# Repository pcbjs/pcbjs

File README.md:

# pcbjs

PCB design as TypeScript and JSX. A board is a TSX module: nets and parts are values, JSX places them, and one compile routes what you leave to the autorouter, fills pours, runs DRC and ERC, and writes Gerbers, drills, a BOM and placement file, all zipped, plus a 2D, 3D and schematic viewer that links every item back to its code. This documentation targets pcbjs 0.1.0.

```sh
npm i -D @pcbjs/pcbjs    # Node 22.12 or newer
```

## Quick start

```sh
npx pcbjs create my-board && cd my-board && npm install
npx pcbjs check              # compile, route, DRC and ERC; one line per finding with the source line to change
npm run dev                  # live viewer on http://localhost:5173
npm run build                # fab set in .pcbjs/fab/my-board, site in .pcbjs/dist
```

`pcbjs create` writes this first board, `pcb.tsx`: a green LED and its resistor on a 20 x 15 mm two-layer board.

```tsx
// Hello: a green LED on a 20 x 15 mm two-layer board, powered from a two-pin header.
// Frame: millimetres, origin at the top-left corner of the outline, x right, y down.
import PCB from '@pcbjs/fab/JLCPCB/2-Layer' // the fab: stackup, rules and LCSC sourcing; swap for another preset such as @pcbjs/fab/OSHPark/2-Layer
import { nets, route } from '@pcbjs/core'
import { PinHeader, R0603, LED0603, roundedRect } from '@pcbjs/lib'

// Nets: one name per net.
const { GND, VCC, LED } = nets()

// Parts: the value, the part numbers, then the net of each pin by name. MPN is the catch-all, MPN:LCSC is what JLCPCB assembles.
const J1 = PinHeader(2)().source({ MPN: 'PEC02SAAN' }).connect({ 1: GND, 2: VCC })
const R1 = R0603('330').source({ MPN: 'RC0603FR-07330RL', 'MPN:LCSC': 'C23138' }).connect({ 1: VCC, 2: LED })
const D1 = LED0603('green').source({ MPN: 'LTST-C190GKT' }).connect({ A: LED, K: GND })

export default (
  <PCB name="Hello" rev="0.1.0">
    {/* outline: 20 x 15 mm with 1 mm corners */}
    <path layer="Edge.Cuts" d={roundedRect(20, 15, 1)} />

    {/* power in: pin 1 GND, pin 2 VCC */}
    <J1 at="3 4.96" />

    {/* the LED and its resistor, in line with J1 pin 2; D1 turned so its anode faces R1 */}
    <R1 at="9 7.5" />
    <D1 at="15 7.5 180deg" />

    {/* routes: .Z() draws a straight track by hand, a route with no chain is left to the autorouter */}
    {route(J1[2], R1[1]).width(0.3).Z()}
    {route(R1[2], D1.A).width(0.3).Z()}
    {route(D1.K, J1[1]).width(0.3)}

    {/* silk */}
    <text layer="F.SilkS" at="10 12" size={1}>
      Hello
    </text>
  </PCB>
)
```

More boards to start from: `npx pcbjs create --list-examples`, and `examples/demo` with Blinky, a board split into schematic, sourcing and layout files. From source, for contributors: clone https://github.com/pcbjs/pcbjs, run `npm install && npm run build`, and read docs/development.md.

## For agents

Read this section, then `pcbjs docs <topic>` for the one topic you need, which is `docs/<topic>.md` here and the same page under https://pcbjs.dev/docs/. Do not read the whole docs folder; `pcbjs docs --grep 'neck|escape'` prints every doc line that matches a word or a regex. `pcbjs skills install` adds the agent skills of `@pcbjs/skills` to the project and registers `pcbjs mcp`, whose tools a harness then prefers to the shell. `pcbjs docs check` reads the check output field by field; `pcbjs docs findings` lists every rule.

### Mental model

- Schematic: `nets()` gives `Net` values; a footprint factory with a value gives a `Part`; `.connect({ … })` binds pins to nets by name and throws at the call when a pin is wrong. Parts are values: make them in `.map` and plain functions, a loop part with `{ ref }`; the constant a part is bound to is its ref, `const R1 = …` is R1, and nothing is numbered.
- Layout: a part is placed as a JSX element, `<R1 at="9 7.5" />`, or `<Place part={LEDS[2]} at="…" />`; `<g name="P3">` makes `U8` also `P3/U8`.
- Routes: `route(a, b)` and a chain from `a`, `.H(x)`, `.via('B.Cu')`, finishing at `b` with `.Z()` for a straight track or, by default, an automatic leg the autorouter lays after everything else. More ends make a tree; `route('3 10').net(VCC).H(9)` is copper without pads.
- Build: one compile gives the board model, DRC, ERC, the fab set and the site. Findings carry position, refs and the source line to change; `pcbjs inspect` prints where parts, pads and nets ended up, in absolute mm.

### Commands

```sh
pcbjs check                         # the loop: compile, route, DRC, ERC of the entries in pcb.config.ts; exit 1 on errors
pcbjs check --json .pcbjs/r.json    # every finding with its id and fingerprint, for scripts
pcbjs inspect U1 GND                # a part's pads, a net's copper; with several entries name the entry first
pcbjs inspect --lengths DATA        # route lengths of a net, pair or match group
pcbjs shot --select U1              # PNGs of the viewer framed on a part, in .pcbjs/shots
pcbjs dev -p 0                      # the session on a free port; Ctrl-C detaches, pcbjs session stop ends it
```

### Rules of thumb

- Iterate with `pcbjs check`, not `build`; ask `pcbjs inspect` for coordinates, never read `board.json` or rotate pads by hand. Declare `defineFootprint` pins inline or `as const`, or pin names lose their types; every pad matches a pin by name or number, or is marked `nc`.
- `keepout()` keeps copper out; the router's `avoid` is only a cost. A `route-failed` finding names the nearest obstacles: add an `X x y` waypoint, raise `priority`, allow more layers, or move a part. `pcbjs patch hold route:<n>` freezes a route you are happy with.
- A pin with several pads routes to the pad nearest the other end, the pad handle `J1['B4']` chooses; pairs are array ends, `route([J1.DP, J1.DN], [U1.DP, U1.DN]).impedance(90)`, and `.length(mm)` and `.match('DATA')` tune lengths.
- KiCad: `kicadFootprint('Package_SO:SOIC-8_3.9x4.9mm_P1.27mm')` in code, `pcbjs import footprint` or `pcbjs import board` as files to edit; STEP models by `pcbjs model add`.

## Docs

### Basics

| Topic | What it covers |
| --- | --- |
| `basics` | a first board end to end, in order, one step per topic below |
| `quickstart` | install, project files, config, the loop |
| `board` | `<PCB>` with `name` and `rev`, units, coordinates, layers |
| `schematic` | nets, parts, names, `.connect`, placing, pin and pad handles |
| `layout` | elements, pads, `pour`, `via`, `keepout`, shapes, text |
| `routing` | route ends, the chain, branches, drawn copper, width and layer |
| `check` | the edit loop, reading `pcbjs check`, exit codes, where files land |
| `editor` | source links, the VS Code extension, panes, hovers and lenses |
| `fab-set` | every file of the fab set, README-fab, BOM and placement |
| `import` | `pcbjs import footprint` and `board`, `kicadFootprint()` |

### Advanced

| Topic | What it covers |
| --- | --- |
| `advanced` | every topic below, grouped |
| `circuits` | circuits, ports, instance indices and refs, layouts |
| `footprints` | `defineFootprint`, `part()`, `withPins`, typing pin and pad names |
| `schematic-graphic` | the schematic drawing, symbols, wires, automatic wiring |
| `sourcing` | `MPN` keys, `.source()`, sourcing tags, BOM resolution |
| `stdlib` | every footprint family with pins and frame, footprint helpers |
| `placement` | `auto` slots, the placer, solvers, costs, followers, freezing |
| `grids` | `defineGrid`, grid units, origins on pads and points, schematic grids, snapping |
| `stackup` | the stackup, its builders, project-wide defaults |
| `fonts` | stroke and outline fonts for `<text>` and their licences |
| `pours` | pour fill, thermal reliefs, islands, `stitch()` |
| `route-options` | builder methods, teardrops, autoroute parameters, net classes |
| `autorouter` | layers, vias, order and rip up, failures, cache and holds |
| `pairs` | differential pairs, gap, impedance, via pairs, pair DRC |
| `length` | length targets, match groups and meanders |
| `patches` | edits by reference, holds, the `.patches.ts` file |
| `rules` | rule values, overrides per pad, part and net, fab rule sets |
| `findings` | every DRC and ERC rule, finding ids, what makes a board orderable |
| `refs` | the reference grammar every surface names things with |
| `testing` | board tests and golden fab sets |
| `fab` | fab presets, `bindPCB`, `variants` |
| `references` | another board as a mechanical reference |
| `3d` | the 3D view, generated part models, the model cache |
| `models` | `pcbjs model add`, align and check, model licences |
| `cli` | every command and flag, the `--json` report |
| `inspect` | every `pcbjs inspect` query and its output |
| `interaction` | UI operations, source boundaries, cancellation and acceptance |
| `viewer` | the 2D and schematic views, panels, multi-board sites |
| `layout-editing` | instance overrides, shared library layouts, source ownership and undo |
| `editing` | the viewer's tools: move, rotate, side and control points, what a drag writes, the assist mode |
| `keys` | every key and gesture of the views, the modifier contract, the command palette |
| `ui` | `@pcbjs/ui`, the views and panels as Vue components, and the `?pcb:` imports for a site of your own |
| `render` | the render spec behind `pcbjs shot` and `session/render`, views, cameras, framing, highlight, marks, the budget |
| `diff` | `pcbjs diff <ref>`, before, after and tinted diff images against a git commit, the pull request comment |
| `vscode` | the extension in depth: attaching, sidebar, commands, settings, drafts |
| `editor-actions` | editor operation ownership, cancellation, undo and availability |
| `highlight` | what the cursor and hover pick, source ranges |
| `session` | the one process `pcbjs dev`, the editor and agents share |
| `workspace` | one session for several projects |
| `queries` | `pcbjs events`, `q`, `script` and the board API |
| `skills` | the agent skills and `pcbjs skills install` |
| `mcp` | `pcbjs mcp`, the MCP server that gives agents the checks, queries, renders and edits as tools |
| `lsp` | `pcbjs lsp --stdio`, the language server for Neovim, Helix, Zed, JetBrains and Claude Code |
| `plugins` | compiler plugins: stages, hooks, checks |
| `browser` | the compiler in a Web Worker, what of it runs in a browser, its equality with Node |
| `library` | `pcbjs build --lib`, a project as a package of parts, circuits and boards, `compose()` |
| `kicad` | what carries over from KiCad and what does not |
| `stackup-and-rules` | the sources behind every stackup and rule value |
| `ide-bridge` | the protocol between the session and an editor |
| `design` | why pcbjs is built the way it is |
| `development` | working on pcbjs itself: packages, build, tests |
| `support` | what is supported, partial and missing, with the evidence for each |

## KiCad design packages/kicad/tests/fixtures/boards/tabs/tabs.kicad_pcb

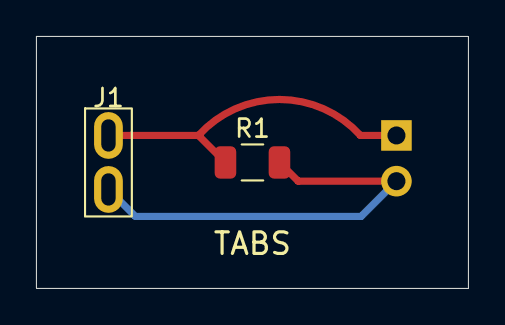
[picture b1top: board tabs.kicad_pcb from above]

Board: 2 copper layers, 24.0 x 14.0 mm, 3 parts (1 on the bottom side), 2 nets.

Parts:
J1: Tabs; Tab_Slot_1x02_P3.00mm
J2: Hdr; Hdr_1x02_P2.54mm
R1: 10k; R_1206

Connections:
GND: J1.2, J2.2, R1.2
SIG: J1.1, J2.1, R1.1

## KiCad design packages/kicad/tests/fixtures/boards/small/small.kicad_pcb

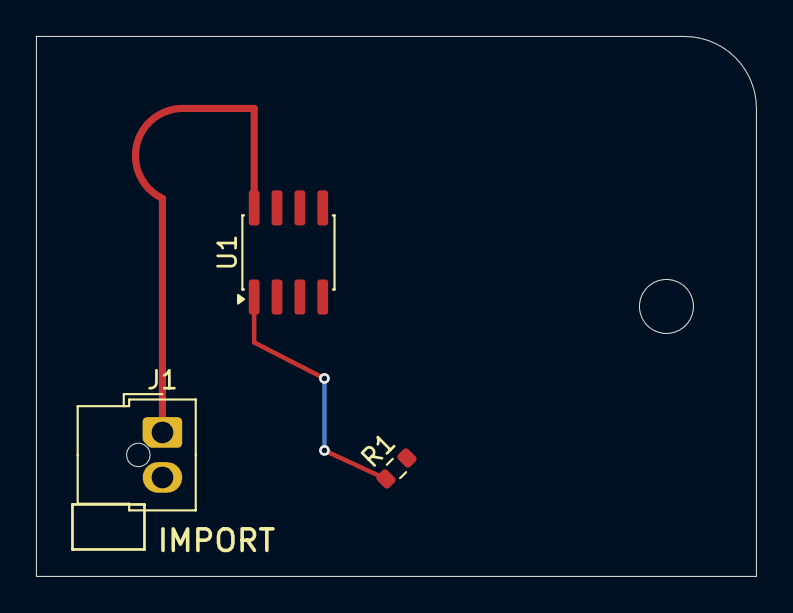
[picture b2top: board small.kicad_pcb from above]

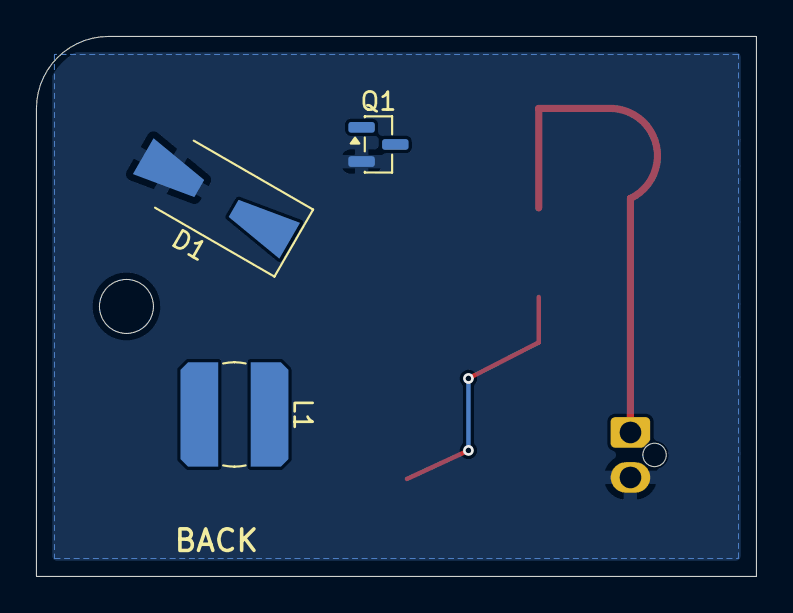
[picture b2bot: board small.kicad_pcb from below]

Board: 2 copper layers, 40.0 x 30.0 mm, 6 parts (3 on the bottom side), 3 nets.

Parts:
D1: SS14; D_SMA-SMB_Universal_Handsoldering
J1: Nano-Fit; Molex_Nano-Fit_105309-xx02_1x02_P2.50mm_Vertical
L1: 10u; L_Bourns_SDR0604
Q1: MMBT3904; SOT-23
R1: 10k; R_0603_1608Metric
U1: LM358; SOIC-8_3.9x4.9mm_P1.27mm

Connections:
GND: D1.2, J1.2, Q1.2, R1.2, U1.4
SIG: L1.1, Q1.1, R1.1, U1.1
VCC: D1.1, J1.1, L1.2, U1.8
